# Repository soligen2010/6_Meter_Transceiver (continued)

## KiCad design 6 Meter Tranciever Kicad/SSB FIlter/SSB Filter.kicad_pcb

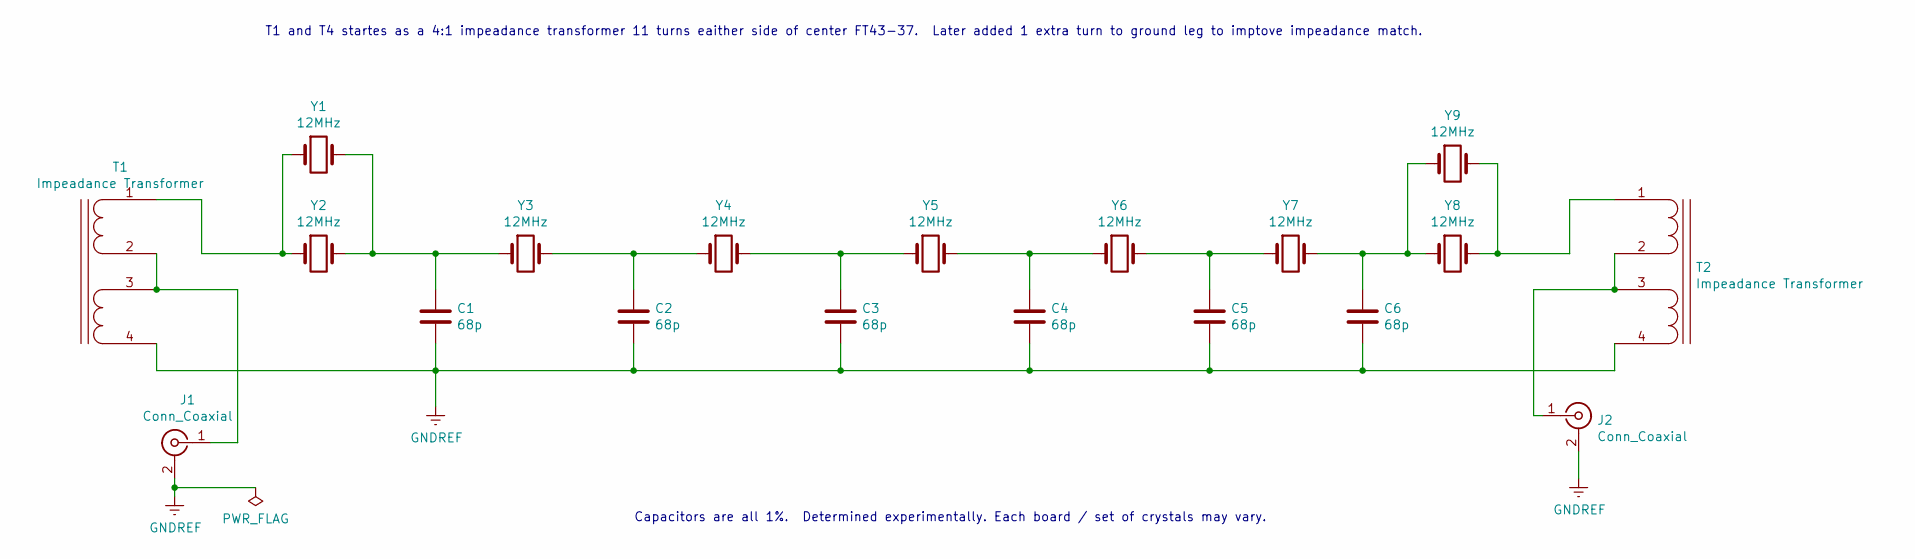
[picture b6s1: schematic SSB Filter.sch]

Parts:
C1, C2, C3, C4, C5, C6: 68p; SMD_Combo_1206_0805
J1, J2: Conn_Coaxial; SMA_Molex_73251-2120_EdgeMount_Horizontal
T1, T2: Impeadance Transformer; T37_AutoTransformerParallel
Y1, Y2, Y3, Y4, Y5, Y6, Y7, Y8, Y9: 12MHz; Crystal_HC49-4H_Vertical

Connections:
GNDREF: C1.2, C2.2, C3.2, C4.2, C5.2, C6.2, J1.2 (Ext), J2.2 (Ext), T1.4 (SD), T2.4 (SD)
unnamed: C1.1, Y1.2, Y2.2, Y3.1
unnamed: C2.1, Y3.2, Y4.1
unnamed: C3.1, Y4.2, Y5.1
unnamed: C4.1, Y5.2, Y6.1
unnamed: C5.1, Y6.2, Y7.1
unnamed: C6.1, Y7.2, Y8.1, Y9.1
unnamed: J1.1 (In), T1.2 (SB), T1.3 (SC)
unnamed: J2.1 (In), T2.2 (SB), T2.3 (SC)
unnamed: T1.1 (SA), Y1.1, Y2.1
unnamed: T2.1 (SA), Y8.2, Y9.2

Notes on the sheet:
Capacitors are all 1%. Determined experimentally. Each board / set of crystals may vary.
T1 and T4 startes as a 4:1 impeadance transformer 11 turns eaither side of center FT43-37. Later added 1 extra turn to ground leg to imptove impeadance match.

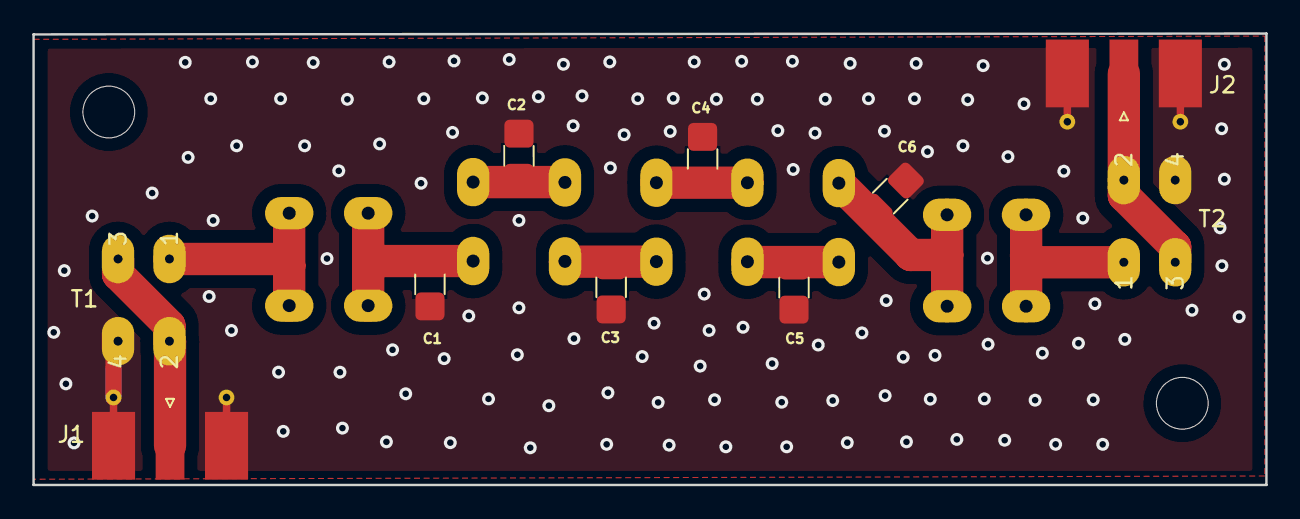
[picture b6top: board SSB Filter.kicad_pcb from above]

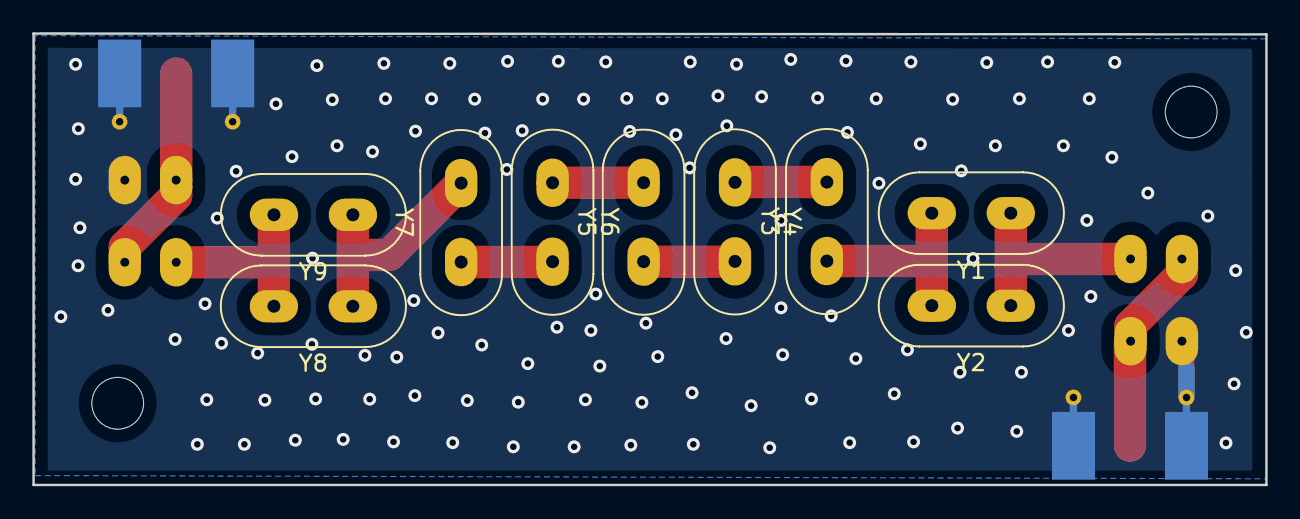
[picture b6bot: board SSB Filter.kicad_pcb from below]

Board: 2 copper layers, 76.2 x 27.9 mm, 21 parts (9 on the bottom side), 11 nets.

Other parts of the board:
 : MountingHole_3.2mm_M3
 #2: MountingHole_3.2mm_M3

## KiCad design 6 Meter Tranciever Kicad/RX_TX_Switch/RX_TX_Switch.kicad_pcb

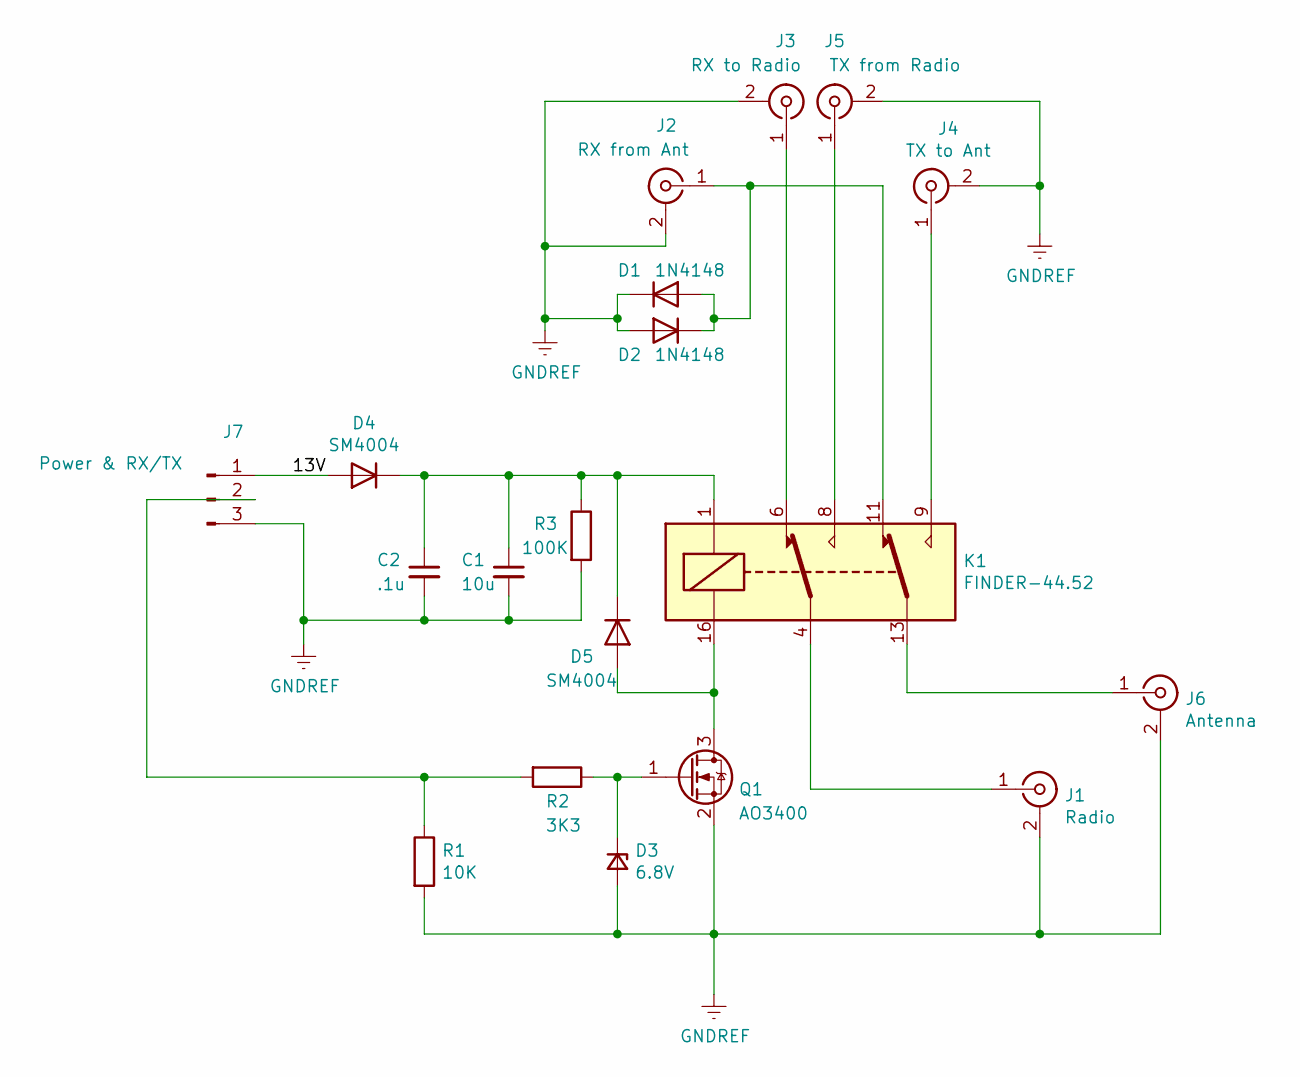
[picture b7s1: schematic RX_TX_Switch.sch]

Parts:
C1: 10u; SMD_Combo_1206_0805
C2: .1u; SMD_Combo_1206_0805
D1, D2: 1N4148; D_SOD-323_HandSoldering
D3: 6.8V; D_MiniMELF_Handsoldering
D4, D5: SM4004; D_SMA_Handsoldering
J1: Radio; SMA_Molex_73251-2120_EdgeMount_Horizontal
J2: RX from Ant; SMA_Molex_73251-2120_EdgeMount_Horizontal
J3: RX to Radio; SMA_Molex_73251-2120_EdgeMount_Horizontal
J4: TX to Ant; SMA_Molex_73251-2120_EdgeMount_Horizontal
J5: TX from Radio; SMA_Molex_73251-2120_EdgeMount_Horizontal
J6: Antenna; SMA_Molex_73251-2120_EdgeMount_Horizontal
J7: Power & RX/TX; FanPinHeader_1x03_P2.54mm_Vertical
K1: FINDER-44.52; Relay_DPDT_Omron_G5V-2
Q1: AO3400; SOT-23_Handsoldering
R1: 10K; SMD_Combo_1206_0805
R2: 3K3; SMD_Combo_1206_0805
R3: 100K; SMD_Combo_1206_0805

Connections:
/13V: D4.2 (A), J7.1
GNDREF: C1.2, C2.2, D1.1 (K), D2.2 (A), D3.2 (A), J1.2 (Ext), J2.2 (Ext), J3.2 (Ext), J4.2 (Ext), J5.2 (Ext), J6.2 (Ext), J7.3, Q1.2 (S), R1.2, R3.2
unnamed: C1.1, C2.1, D4.1 (K), D5.1 (K), K1.1, R3.1
unnamed: D1.2 (A), D2.1 (K), J2.1 (In), K1.11
unnamed: D3.1 (K), Q1.1 (G), R2.1
unnamed: D5.2 (A), K1.16, Q1.3 (D)
unnamed: J1.1 (In), K1.4
unnamed: J3.1 (In), K1.6
unnamed: J4.1 (In), K1.9
unnamed: J5.1 (In), K1.8
unnamed: J6.1 (In), K1.13
unnamed: J7.2, R1.1, R2.2

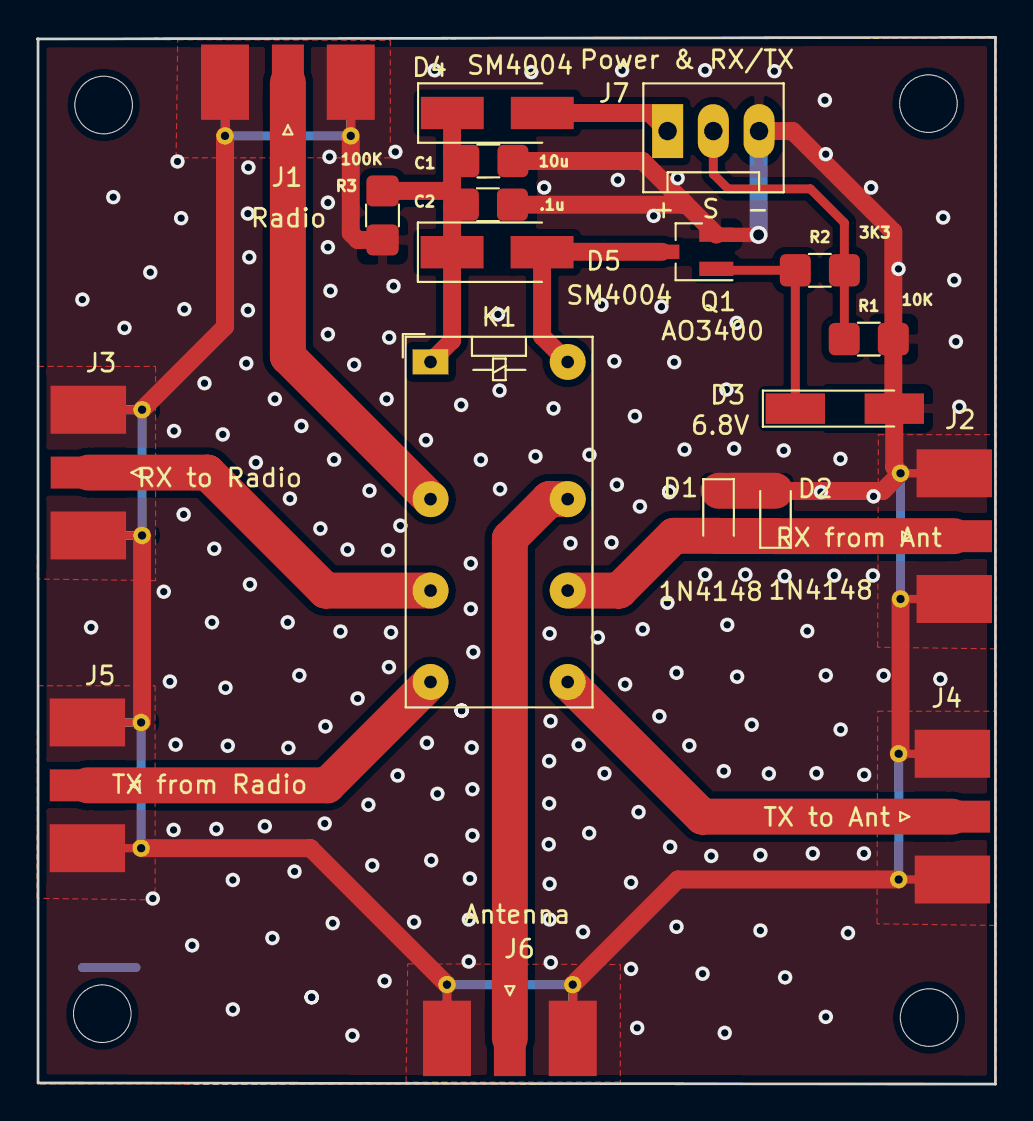
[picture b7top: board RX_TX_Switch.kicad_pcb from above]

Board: 2 copper layers, 53.2 x 58.2 mm, 23 parts (0 on the bottom side), 12 nets.

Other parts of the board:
 : MountingHole_3.2mm_M3
 #2,  #3,  #4: MountingHole_3.2mm_M3

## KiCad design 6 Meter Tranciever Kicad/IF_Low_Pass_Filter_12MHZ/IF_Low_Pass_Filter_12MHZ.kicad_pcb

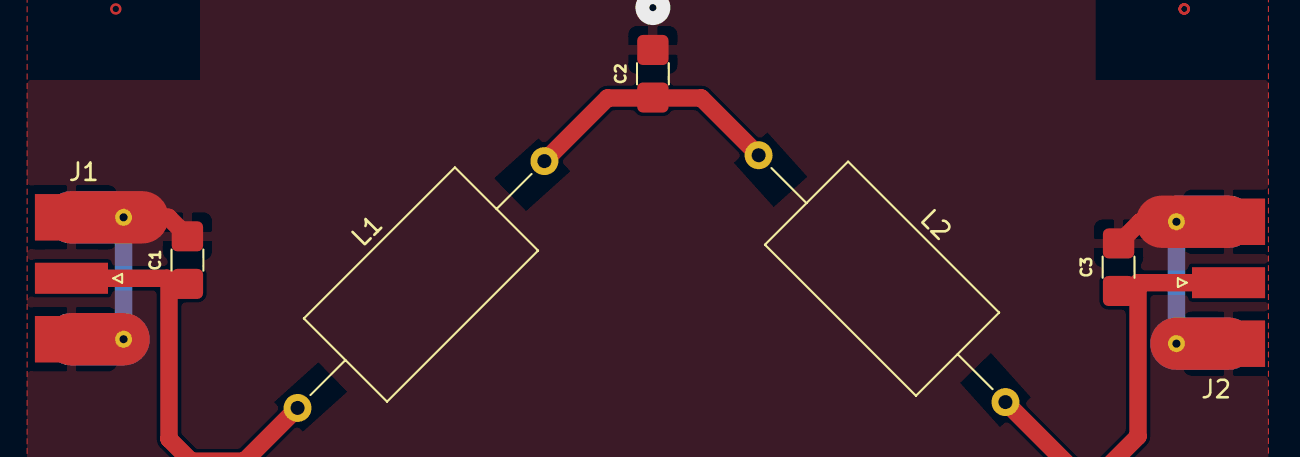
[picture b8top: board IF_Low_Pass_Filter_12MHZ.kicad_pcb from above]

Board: 2 copper layers, 7 parts (0 on the bottom side), 4 nets.

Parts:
C1, C3: 270p; SMD_Combo_1206_0805
C2: 470p; SMD_Combo_1206_0805
J1, J2: SMA; SMA_Molex_73251-2120_EdgeMount_Horizontal
L1, L2: 820n; C_Axial_L12.0mm_D6.5mm_P20.00mm_Horizontal

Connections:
GNDREF: C1.2, C2.2, C3.2, J1.2, J2.2
unnamed: C1.1, J1.1, L1.1
unnamed: C2.1, L1.2, L2.1
unnamed: C3.1, J2.1, L2.2

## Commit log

2022-02-27 Initial Copy
    Copying initial version
2022-02-27 Status Update
    2022-2-27 Status
2022-02-27 Readme Update
    File Name Without Spaces
2022-02-27 Readme update
    Typo
2022-03-01 Board tweaks
    Board tweaks and remove bak files
2025-02-22 Audio Amp
    Audio Amp
